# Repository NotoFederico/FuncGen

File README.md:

# WiFi Function and Arbitrary Waveforms Generator

---

---

### Download
| Latest release | Latest development build |
|----------------|--------------------------|
|  |  |

---

# Contents
- 1 - [Introduction](#1-introduction)
- 2 - [Paper Link](#3-paper-link)
- 3 - [Contributing](#4-contributing)
- 4 - [Licence](#5-licence)

---

# 1. Introduction

The present project aims to develop a function generator, which is exactly what its name implies: a test equipment that generates electrical signals in the form of waves that are used as stimuli for electronic measurements.

Most circuits require some type of input signal whose amplitude varies with time. The signal can be an alternating current signal (with peaks that oscillate above and below a reference) or it can vary over a range of direct current offset voltages, either positive or negative. It can be a sine wave or other analog function, a digital pulse, a binary pattern, or a purely arbitrary waveform.

The generator of signals, or functions, is the source of stimulus. Pair with a data acquisition instrument for a complete measurement solution. The two tools are connected to the input and output terminals of the device under test (DUT).

The signal generator can provide "ideal" waveforms, or it can add known and repeatable amounts and types of distortion (or errors) to the signal it delivers. This feature is one of the greatest virtues of the signal generator, as it is often impossible to create predictable distortion, exactly when and where it is needed, using only the circuit itself. The response of the device under test (DUT) in the presence of these distorted signals reveals its ability to handle voltages that fall outside the envelope of normal performance.

There are hundreds of different applications for this class of equipment, but placed in a context of electronic measurements, three categories can be divided: Verification: the designers of wireless equipment that develop new transmitting and receiving hardware must simulate baseband I&Q signals, with and without deficiencies, to verify compliance with proprietary wireless standards using arbitrary low-distortion functions.

Characterization: Newly developed digital-to-analog converters (DACs) and analog-to-digital converters (ADCs) must be thoroughly tested for their limits for linearity and distortion. Analog and digital signals are applied in phase to bring the speeds of these devices up to 1Gbps. Stress or margin test: engineers working with serial data flow architectures (commonly used in digital communication buses) need to stress their devices with deficiencies, particularly fluctuations and synchronization violations

In the project in question, known signals can be generated: such as sine, semi-diverse, square, rectangular, triangular, sawtooth and white noise and arbitrary signals, which are those signals of complex origin that do not follow a regular mathematical expression and that can be generated by the user using specialized software and subsequently sent over WiFi, thanks to a dedicated website. These signals can be chosen through a menu and their parameters, such as duty, offset and amplitude, are modifiable and will be monitored in real time on a display.

---

# 2. Paper Link

[Paper (Spanish)](https://github.com/NotoFederico/FuncGen/blob/main/FuncGen_STM32DISCO/Informe.pdf)

---

# 3. Contributing

FuncGen uses the [gitflow workflow](https://www.atlassian.com/git/tutorials/comparing-workflows#gitflow-workflow). If you are implementing a new feature or logic from the original game, please branch off and perform pull requests to ```develop```. If you are fixing a bug for the next release, please branch off and perform pull requests to the correct release branch. ```master``` only contains tagged releases, you should never branch off this.

---

# 4. Licence

FuncGen is licensed under the GNU General Public License version 3.

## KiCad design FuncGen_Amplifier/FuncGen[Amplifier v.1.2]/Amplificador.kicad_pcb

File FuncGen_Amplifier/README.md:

# FuncGen_Amplifier

Sistema operativo: Windows 10 / Software: Kicad

Modulo selector, amplificador y conversor de las señales generadas por el módulo principal del generador de funciones y ondas arbitrarias WiFi

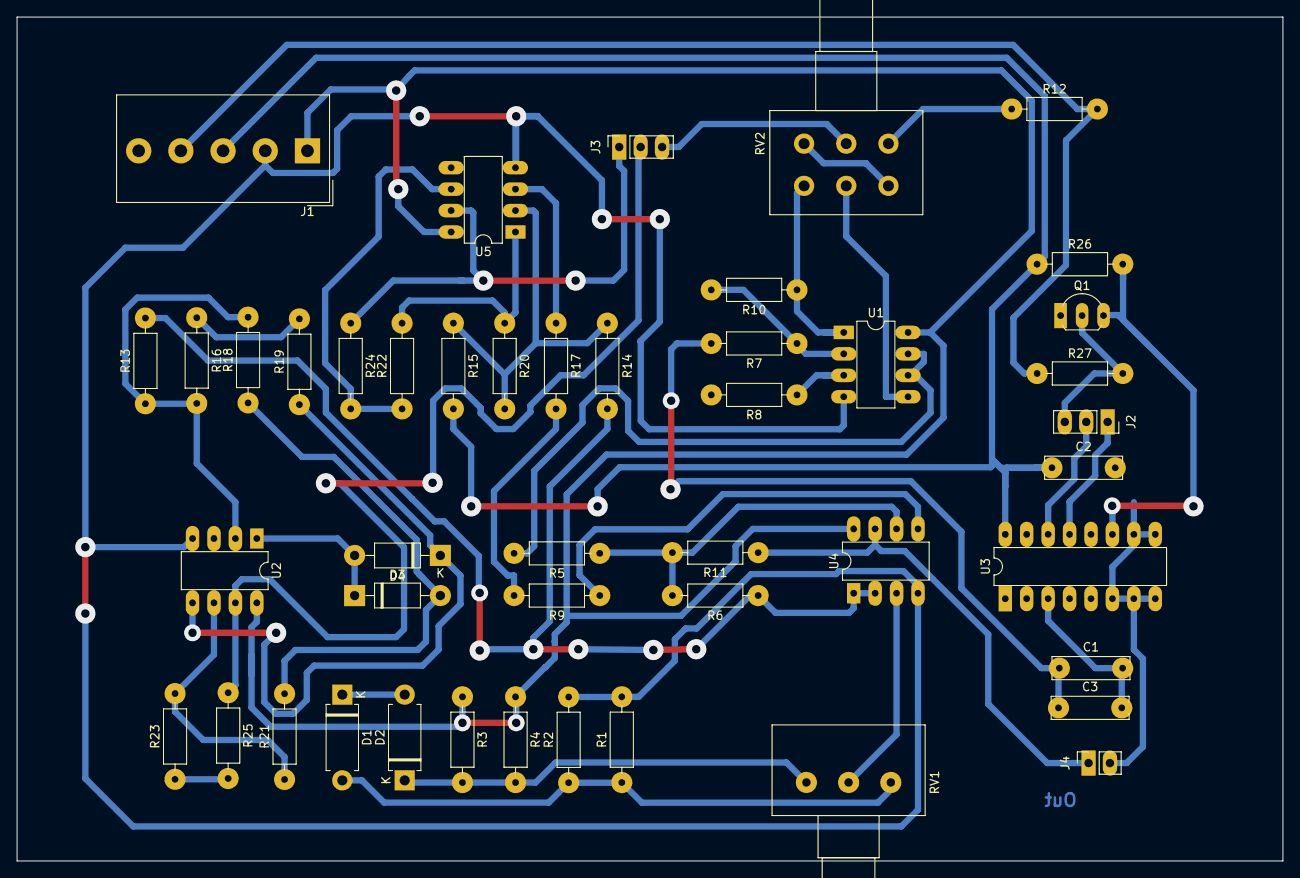
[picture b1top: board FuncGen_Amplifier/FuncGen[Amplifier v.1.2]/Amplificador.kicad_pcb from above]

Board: 2 copper layers, 150.0 x 100.0 mm, 46 parts (0 on the bottom side), 38 nets.

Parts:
C1: 100n; C_Rect_L9.0mm_W2.5mm_P7.50mm_MKT
C2, C3: 100nF; C_Rect_L9.0mm_W2.5mm_P7.50mm_MKT
D1, D2: D_Zener; D_DO-15_P10.16mm_Horizontal
D3, D4: 1N4007; D_DO-41_SOD81_P10.16mm_Horizontal
J1: Screw_Terminal_01x05; Altech_AK300_1x05_P5.00mm_45-Degree
J2, J3: Conn_01x03_Male; PinSocket_1x03_P2.54mm_Vertical
J4: Conn_01x02_Male; PinSocket_1x02_P2.54mm_Vertical
Q1: BF245B; TO-92L_Inline_Wide
R1, R3: 8.2k; R_Axial_DIN0207_L6.3mm_D2.5mm_P10.16mm_Horizontal
R2, R4: 47k; R_Axial_DIN0207_L6.3mm_D2.5mm_P10.16mm_Horizontal
R5, R6, R8, R9, R11, R12, R13, R17, R18, R20, R21, R22, R24, R26, R27: 10k; R_Axial_DIN0207_L6.3mm_D2.5mm_P10.16mm_Horizontal
R7: 5.6k; R_Axial_DIN0207_L6.3mm_D2.5mm_P10.16mm_Horizontal
R10, R14, R15: 33k; R_Axial_DIN0207_L6.3mm_D2.5mm_P10.16mm_Horizontal
R16, R23: 3.3k; R_Axial_DIN0207_L6.3mm_D2.5mm_P10.16mm_Horizontal
R19, R25: 2.7k; R_Axial_DIN0207_L6.3mm_D2.5mm_P10.16mm_Horizontal
RV1: 10k; Potentiometer_Alps_RK163_Single_Horizontal
RV2: 100k; Potentiometer_Alps_RK163_Dual_Horizontal
U1, U2, U4, U5: TL072; DIP-8_W7.62mm_LongPads
U3: CD4051B; DIP-16_W7.62mm_LongPads

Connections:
/+3.3V: J1.4, R12.2, R27.1
/+5V: C2.1, J1.3, R15.2, R26.1, U3.16
/+12V: J1.1, R3.1, R4.1, U1.8, U2.8, U4.8, U5.8
/-12V: J1.2, R1.2, R2.2, U1.4, U2.4, U4.4, U5.4
/A: Q1.3, R26.2, U3.11
/AmpDac: J3.3, RV2.2
/AmpOut: R5.2, U1.6, U1.7
/ChSelect: J2.3, Q1.2, R27.2
/DACInput: J2.1, U3.13
/Input: C1.2, C3.2, U3.3
/OffsetDac: J3.2, R25.1, U2.7
/OffsetOut: R6.1, R13.2, R14.2, U4.1, U4.2
/Output: J4.1, R11.1, U4.7
/PWMInput: J2.2, U3.14
/PolarityDac: J3.1, R24.1, U5.7
GND: C2.2, D1.1, D2.2, J1.5, J4.2, Q1.1, R8.2, R9.2, R17.2, RV2.3, RV2.4, U2.3, U3.6, U3.7, U3.8, U3.9, U3.10, U5.5
unnamed: C1.1, C3.1, R7.2
unnamed: D1.2, R1.1, R2.1, RV1.3
unnamed: D2.1, R3.2, R4.2, RV1.1
unnamed: D3.1, D4.2, U2.1
unnamed: D3.2, R18.1, R21.2
unnamed: D4.1, R19.1, U2.5
unnamed: R8.1, U1.3
unnamed: R9.1, U4.5
unnamed: R10.1, RV2.6, U1.1
unnamed: R7.1, R10.2, U1.2
unnamed: R5.1, R6.2, R11.2, U4.6
unnamed: R12.1, RV2.1
unnamed: R13.1, R16.2, R18.2, U2.2
unnamed: R14.1, R15.1, R20.2, U5.2
unnamed: R16.1, R19.2
unnamed: R17.1, U5.3
unnamed: R20.1, R22.2, U5.1
unnamed: R21.1, R23.2, U2.6
unnamed: R22.1, R24.2, U5.6
unnamed: R23.1, R25.2
unnamed: RV1.2, U4.3
unnamed: RV2.5, U1.5

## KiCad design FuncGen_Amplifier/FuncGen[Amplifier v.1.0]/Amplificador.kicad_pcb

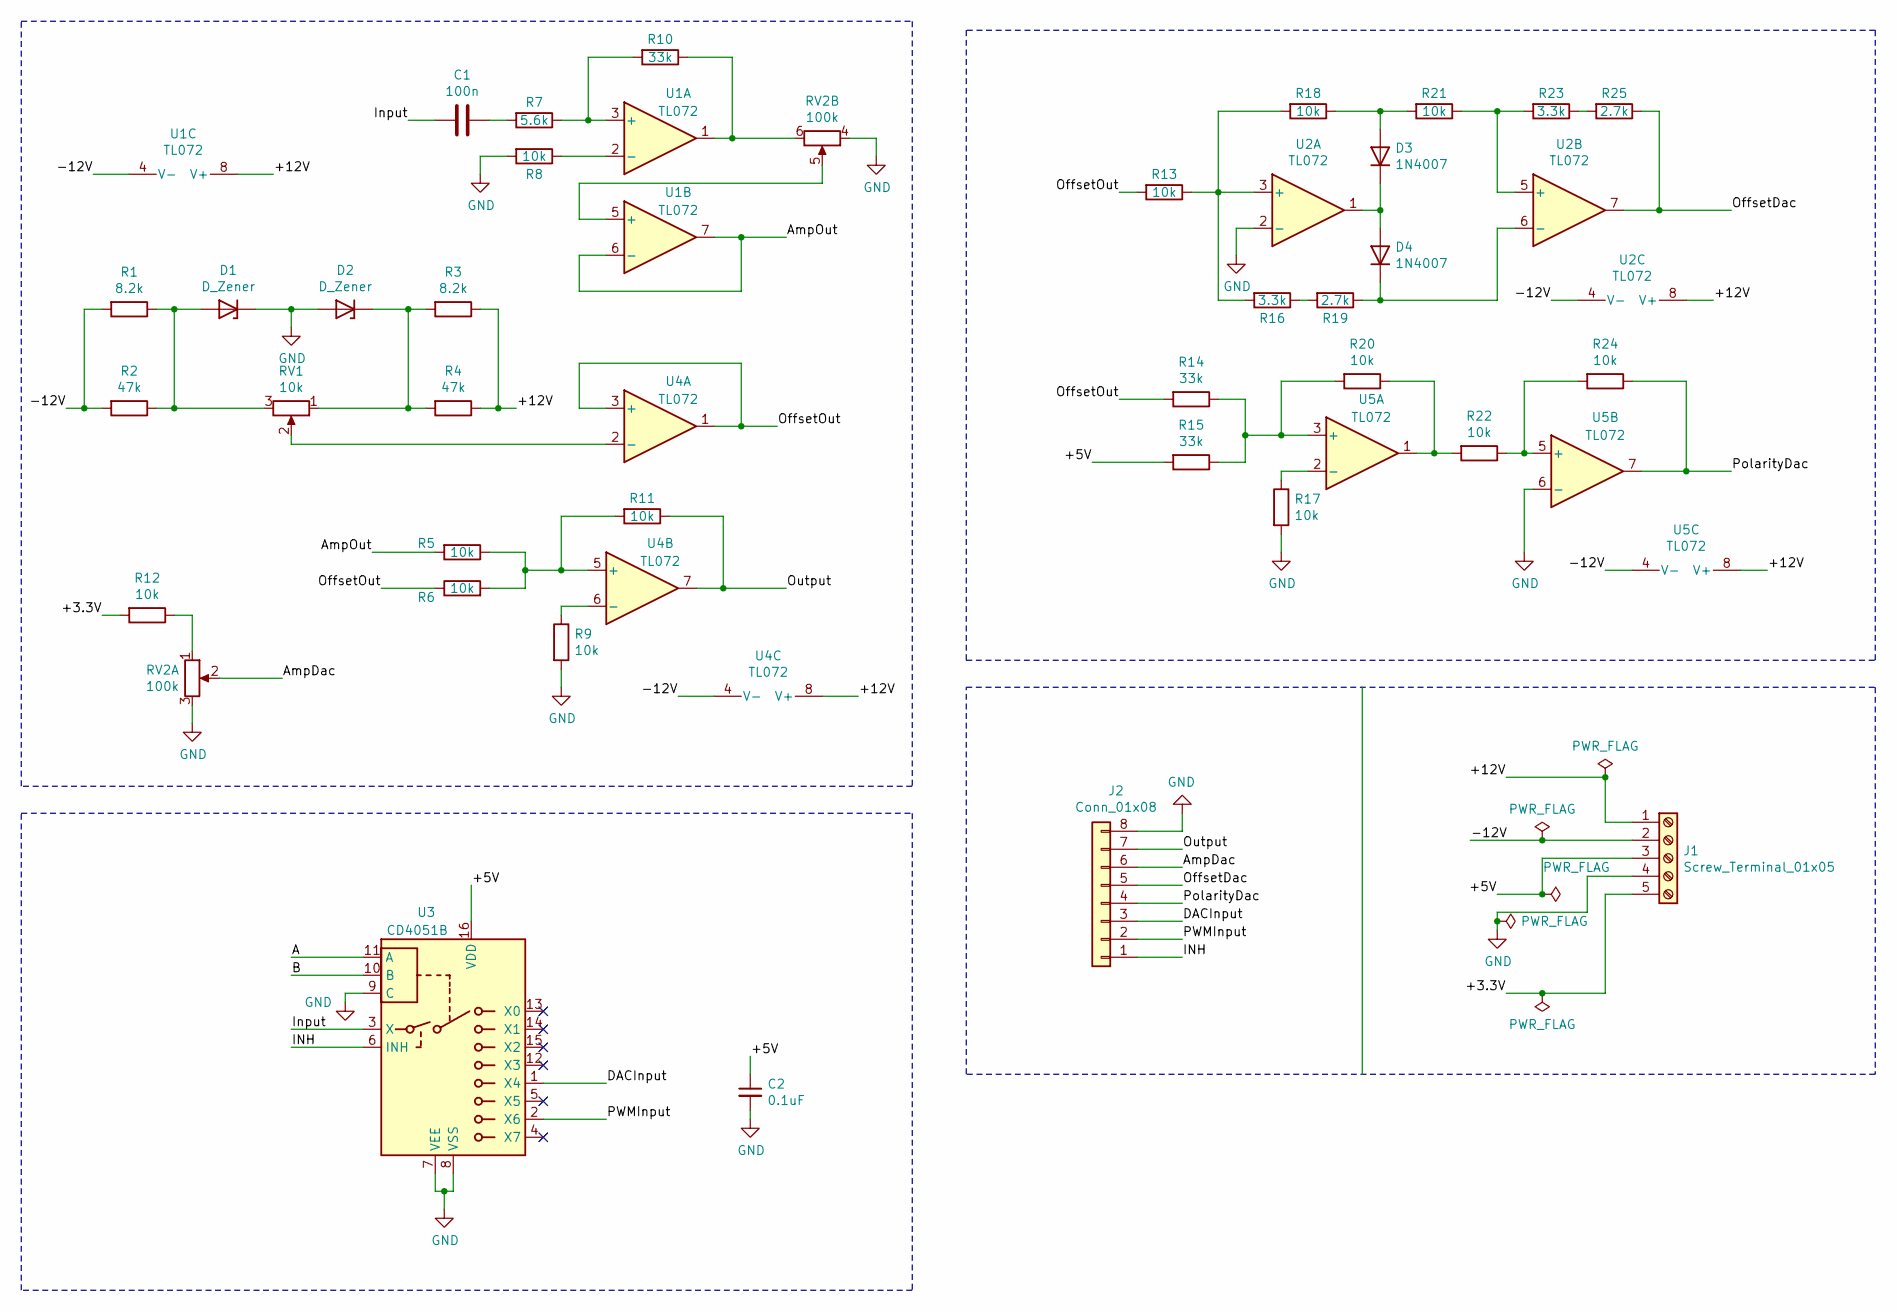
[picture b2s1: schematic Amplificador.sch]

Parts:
C1: 100n; C_Rect_L9.0mm_W2.5mm_P7.50mm_MKT
C2: 0.1uF; C_Rect_L9.0mm_W2.5mm_P7.50mm_MKT
D1, D2: D_Zener; D_DO-15_P10.16mm_Horizontal
D3, D4: 1N4007; D_DO-41_SOD81_P10.16mm_Horizontal
J1: Screw_Terminal_01x05; Altech_AK300_1x05_P5.00mm_45-Degree
J2: Conn_01x08; PinHeader_1x08_P2.54mm_Vertical
R1, R3: 8.2k; R_Axial_DIN0207_L6.3mm_D2.5mm_P10.16mm_Horizontal
R2, R4: 47k; R_Axial_DIN0207_L6.3mm_D2.5mm_P10.16mm_Horizontal
R5, R6, R8, R9, R11, R12, R13, R17, R18, R20, R21, R22, R24: 10k; R_Axial_DIN0207_L6.3mm_D2.5mm_P10.16mm_Horizontal
R7: 5.6k; R_Axial_DIN0207_L6.3mm_D2.5mm_P10.16mm_Horizontal
R10, R14, R15: 33k; R_Axial_DIN0207_L6.3mm_D2.5mm_P10.16mm_Horizontal
R16, R23: 3.3k; R_Axial_DIN0207_L6.3mm_D2.5mm_P10.16mm_Horizontal
R19, R25: 2.7k; R_Axial_DIN0207_L6.3mm_D2.5mm_P10.16mm_Horizontal
RV1: 10k; Potentiometer_Alps_RK163_Single_Horizontal
RV2: 100k; Potentiometer_Alps_RK163_Dual_Horizontal
U1, U2, U4, U5: TL072; DIP-8_W7.62mm_LongPads
U3: CD4051B; DIP-16_W7.62mm_LongPads

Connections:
/+3.3V: J1.5, R12.2
/+5V: C2.1, J1.3, R15.2, U3.16 (VDD)
/+12V: J1.1, R3.1, R4.1, U1.8 (V+), U2.8 (V+), U4.8 (V+), U5.8 (V+)
/-12V: J1.2, R1.2, R2.2, U1.4 (V-), U2.4 (V-), U4.4 (V-), U5.4 (V-)
/A: U3.11 (A)
/AmpDac: J2.6, RV2.2
/AmpOut: R5.2, U1.6 (-), U1.7
/B: U3.10 (B)
/DACInput: J2.3, U3.1 (X4)
/INH: J2.1, U3.6 (INH)
/Input: C1.2, U3.3 (X)
/OffsetDac: J2.5, R25.1, U2.7
/OffsetOut: R6.1, R13.2, R14.2, U4.1, U4.3 (+)
/Output: J2.7, R11.1, U4.7
/PWMInput: J2.2, U3.2 (X6)
/PolarityDac: J2.4, R24.1, U5.7
GND: C2.2, D1.1 (K), D2.2 (A), J1.4, J2.8, R8.2, R9.2, R17.2, RV2.3, RV2.4, U2.2 (-), U3.7 (VEE), U3.8 (VSS), U3.9 (C), U5.6 (-)
unnamed: C1.1, R7.2
unnamed: D1.2 (A), R1.1, R2.1, RV1.3
unnamed: D2.1 (K), R3.2, R4.2, RV1.1
unnamed: D3.1 (K), D4.2 (A), U2.1
unnamed: D3.2 (A), R18.1, R21.2
unnamed: D4.1 (K), R19.1, U2.6 (-)
unnamed: R8.1, U1.2 (-)
unnamed: R9.1, U4.6 (-)
unnamed: R10.1, RV2.6, U1.1
unnamed: R7.1, R10.2, U1.3 (+)
unnamed: R5.1, R6.2, R11.2, U4.5 (+)
unnamed: R12.1, RV2.1
unnamed: R13.1, R16.2, R18.2, U2.3 (+)
unnamed: R14.1, R15.1, R20.2, U5.3 (+)
unnamed: R16.1, R19.2
unnamed: R17.1, U5.2 (-)
unnamed: R20.1, R22.2, U5.1
unnamed: R21.1, R23.2, U2.5 (+)
unnamed: R22.1, R24.2, U5.5 (+)
unnamed: R23.1, R25.2
unnamed: RV1.2, U4.2 (-)
unnamed: RV2.5, U1.5 (+)

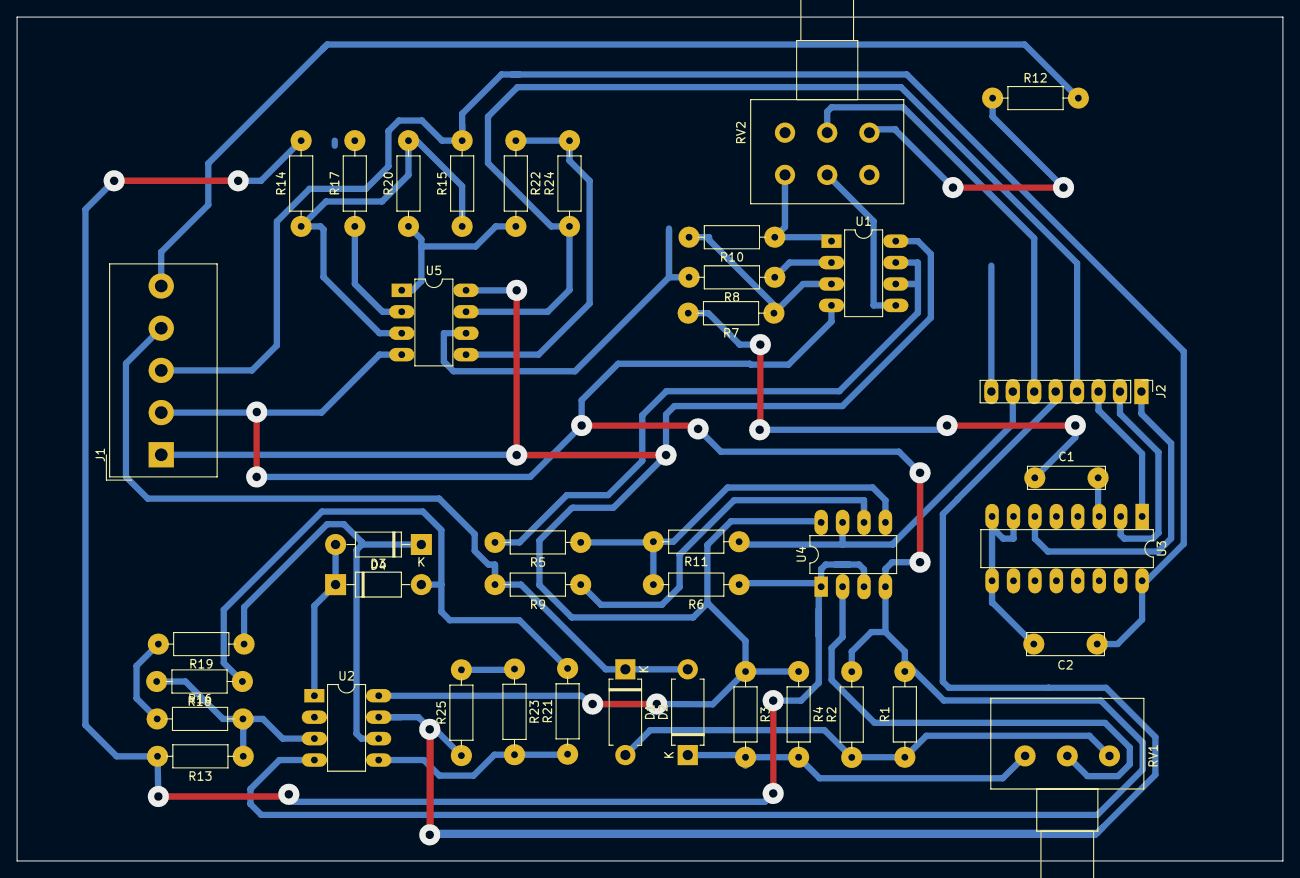
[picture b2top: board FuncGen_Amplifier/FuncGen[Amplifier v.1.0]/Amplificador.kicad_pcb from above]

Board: 2 copper layers, 150.0 x 100.0 mm, 40 parts (0 on the bottom side), 37 nets.
